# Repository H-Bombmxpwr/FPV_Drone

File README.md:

# FPV Drone Project - ECE 445

This repository contains the design and implementation files for the FPV (First-Person View) Drone project developed by Hunter, Eli, and Griffin for the ECE 445 final project at the University of Illinois in the Spring of 2024.

## Project Overview

The FPV Drone project aims to create a robust and user-friendly drone capable of transmitting real-time video to the user, providing an immersive flying experience. This project was proposed by John M. Hart from the center of Autonomy at the University of Illinois. This repository includes everything that was used in one way or another to make this project. 

## Directories

- Code
   - Low level arduino and c code for flashing the microcontrollers 
- crazyflie_control
   - Software to control the Crazyflie Drone
   - Firmware to flash the Crazyflie Done
   - Extensive debugging tools for setup
- Documents
   - Power Points
   - Design Documents
   - PCB schematics and gerbers
   - Images
   - Personal notes
   - Needed Documentation

## Getting Started
If you are looking to control the drone with your computer you will need:
- Crazyflie 2.0 Drone
- Crazyradio or Crazyflie PA
- Gaming Controller Controller

Then follow the list of steps in [install.md](install.md). 

## The Project

It can be found at this [link](https://courses.engr.illinois.edu/ece445/projects.asp) under "Spring 2024". We were team 64. To save time some material is also linked below:

- [Design Document](Documents/documentation/Design_Document_ECE_445.pdf)
- [Video](https://youtu.be/XnW3fZcY0gs)
- [Final Paper](Documents/documentation/ECE_445_Final_Paper_ECE445.pdf)

## Acknowledgments

- Jon Hart
- Dennis McCann
- Tianxiang Zheng
- Bitlooney

Project Link: [https://github.com/H-Bombmxpwr/FPV_Drone](https://github.com/H-Bombmxpwr/FPV_Drone)

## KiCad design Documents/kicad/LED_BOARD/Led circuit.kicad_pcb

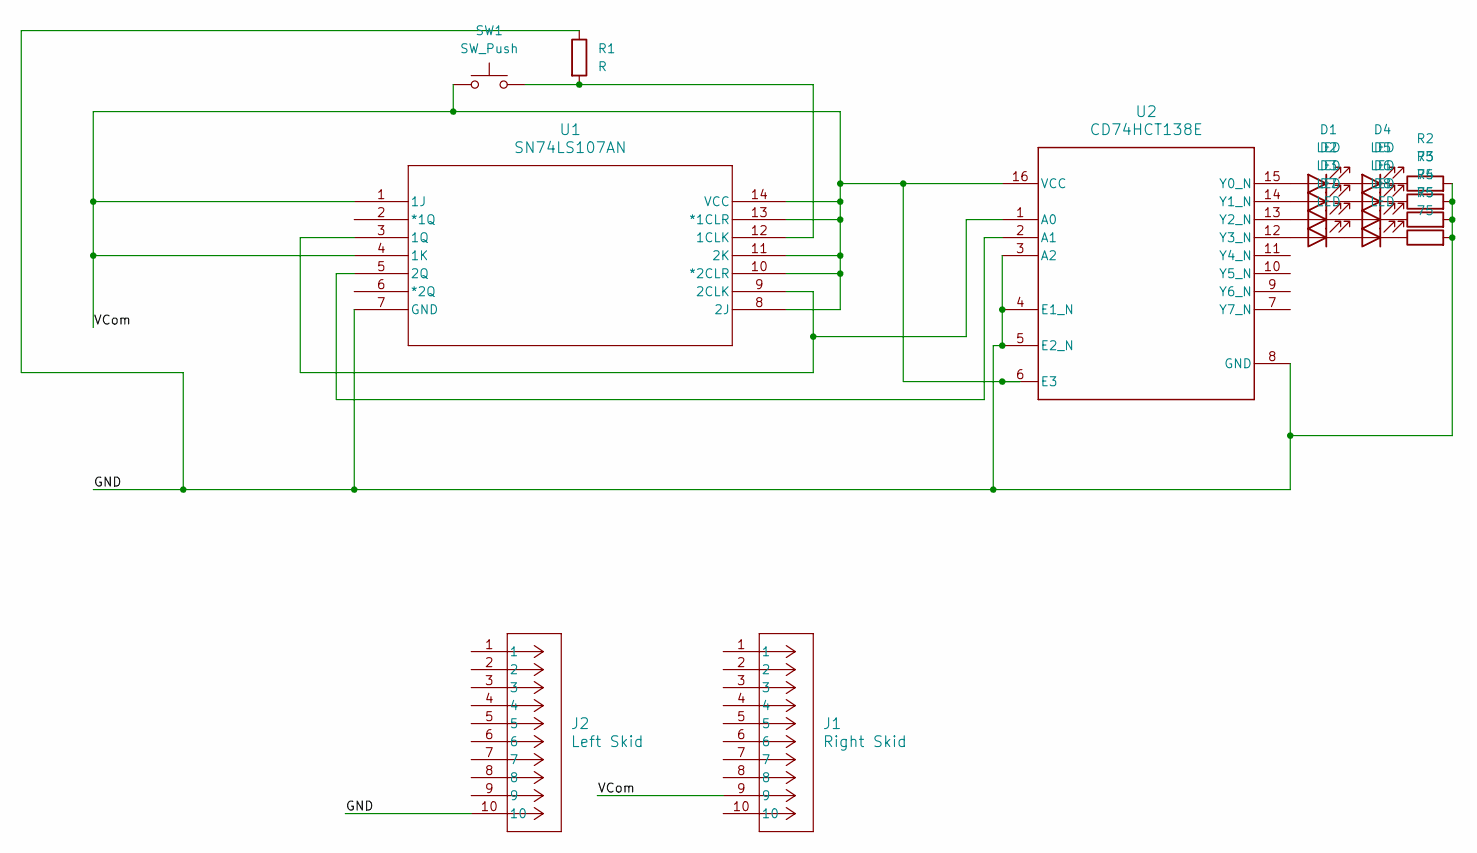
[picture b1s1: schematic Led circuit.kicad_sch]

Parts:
D1, D2, D3, D4, D5, D6, D7, D8: LED; LED_D2.0mm_W4.8mm_H2.5mm_FlatTop
J1: Right Skid; Connector
J2: Left Skid; Connector
R1: R
R2, R3, R4, R5: 75; R_0805_2012Metric_Pad1.20x1.40mm_HandSolder
SW1: SW_Push
U1: SN74LS107AN
U2: CD74HCT138E

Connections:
/GND: J2.10, R1.1, R2.2, R3.2, R4.2, R5.2, U1.7 (GND), U2.3 (A2), U2.4 (E1_N), U2.5 (E2_N), U2.8 (GND); also elsewhere on the board
/VCom: J1.9, SW1.1, U1.1 (1J), U1.4 (1K), U1.8 (2J), U1.10 (*2CLR), U1.11 (2K), U1.13 (*1CLR), U1.14 (VCC), U2.6 (E3), U2.16 (VCC)
unnamed: D1.2 (A), U2.15 (Y0_N)
unnamed: D1.1 (K), D4.2 (A)
unnamed: D2.2 (A), U2.14 (Y1_N)
unnamed: D2.1 (K), D5.2 (A)
unnamed: D3.2 (A), U2.13 (Y2_N)
unnamed: D3.1 (K), D6.2 (A)
unnamed: D4.1 (K), R2.1
unnamed: D5.1 (K), R3.1
unnamed: D6.1 (K), R4.1
unnamed: D7.2 (A), U2.12 (Y3_N)
unnamed: D7.1 (K), D8.2 (A)
unnamed: D8.1 (K), R5.1
unnamed 14: R1.2, SW1.2, U1.12 (1CLK); also elsewhere on the board
unnamed: U1.3 (1Q), U1.9 (2CLK), U2.1 (A0)
unnamed: U1.5 (2Q), U2.2 (A1)

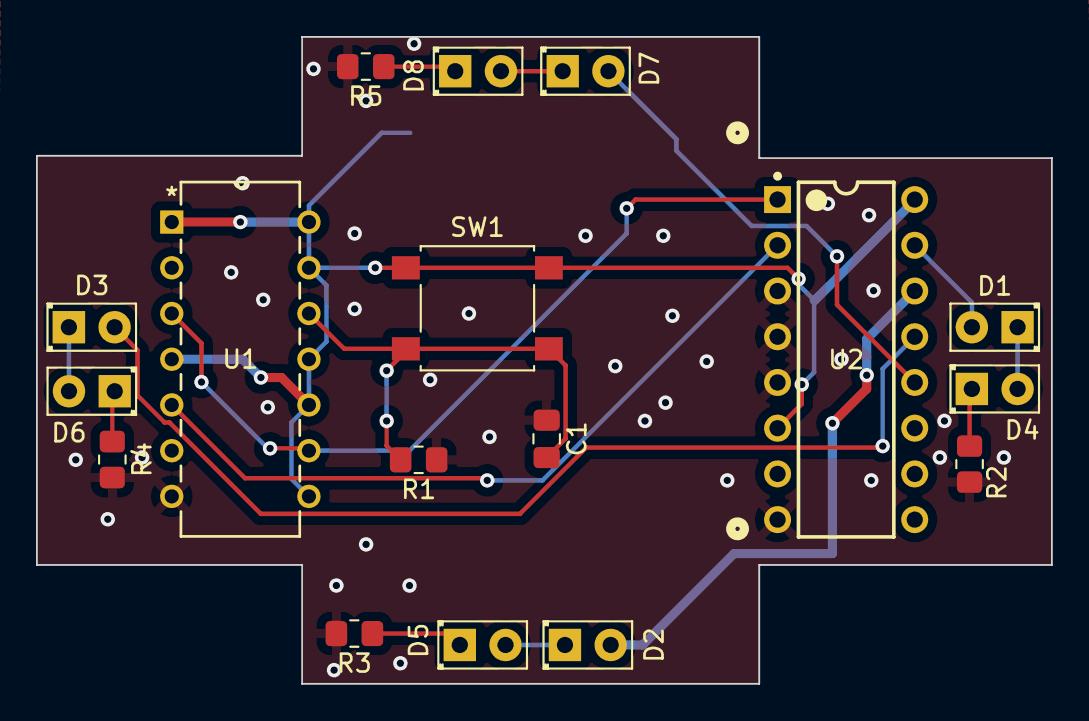
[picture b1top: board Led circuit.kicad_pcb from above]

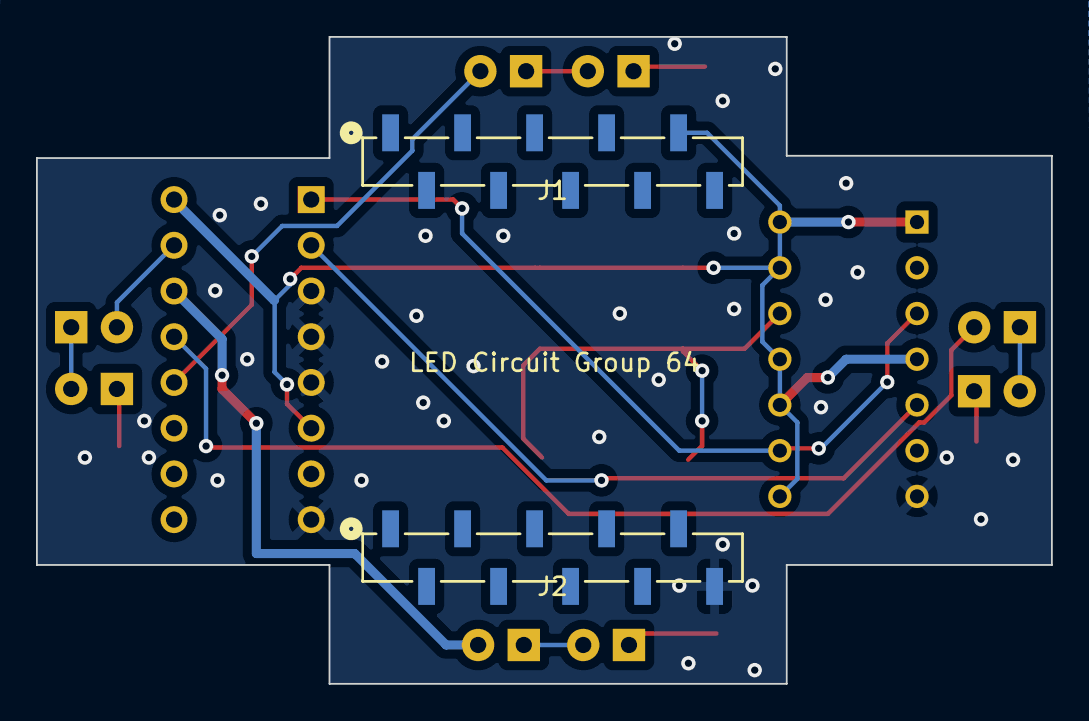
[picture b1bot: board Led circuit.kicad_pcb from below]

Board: 2 copper layers, 56.4 x 35.9 mm, 19 parts (2 on the bottom side), 17 nets.

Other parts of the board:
C1: C; C_0805_2012Metric_Pad1.18x1.45mm_HandSolder

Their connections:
/GND: C1.1; also elsewhere on the board
unnamed 14: C1.2; also elsewhere on the board

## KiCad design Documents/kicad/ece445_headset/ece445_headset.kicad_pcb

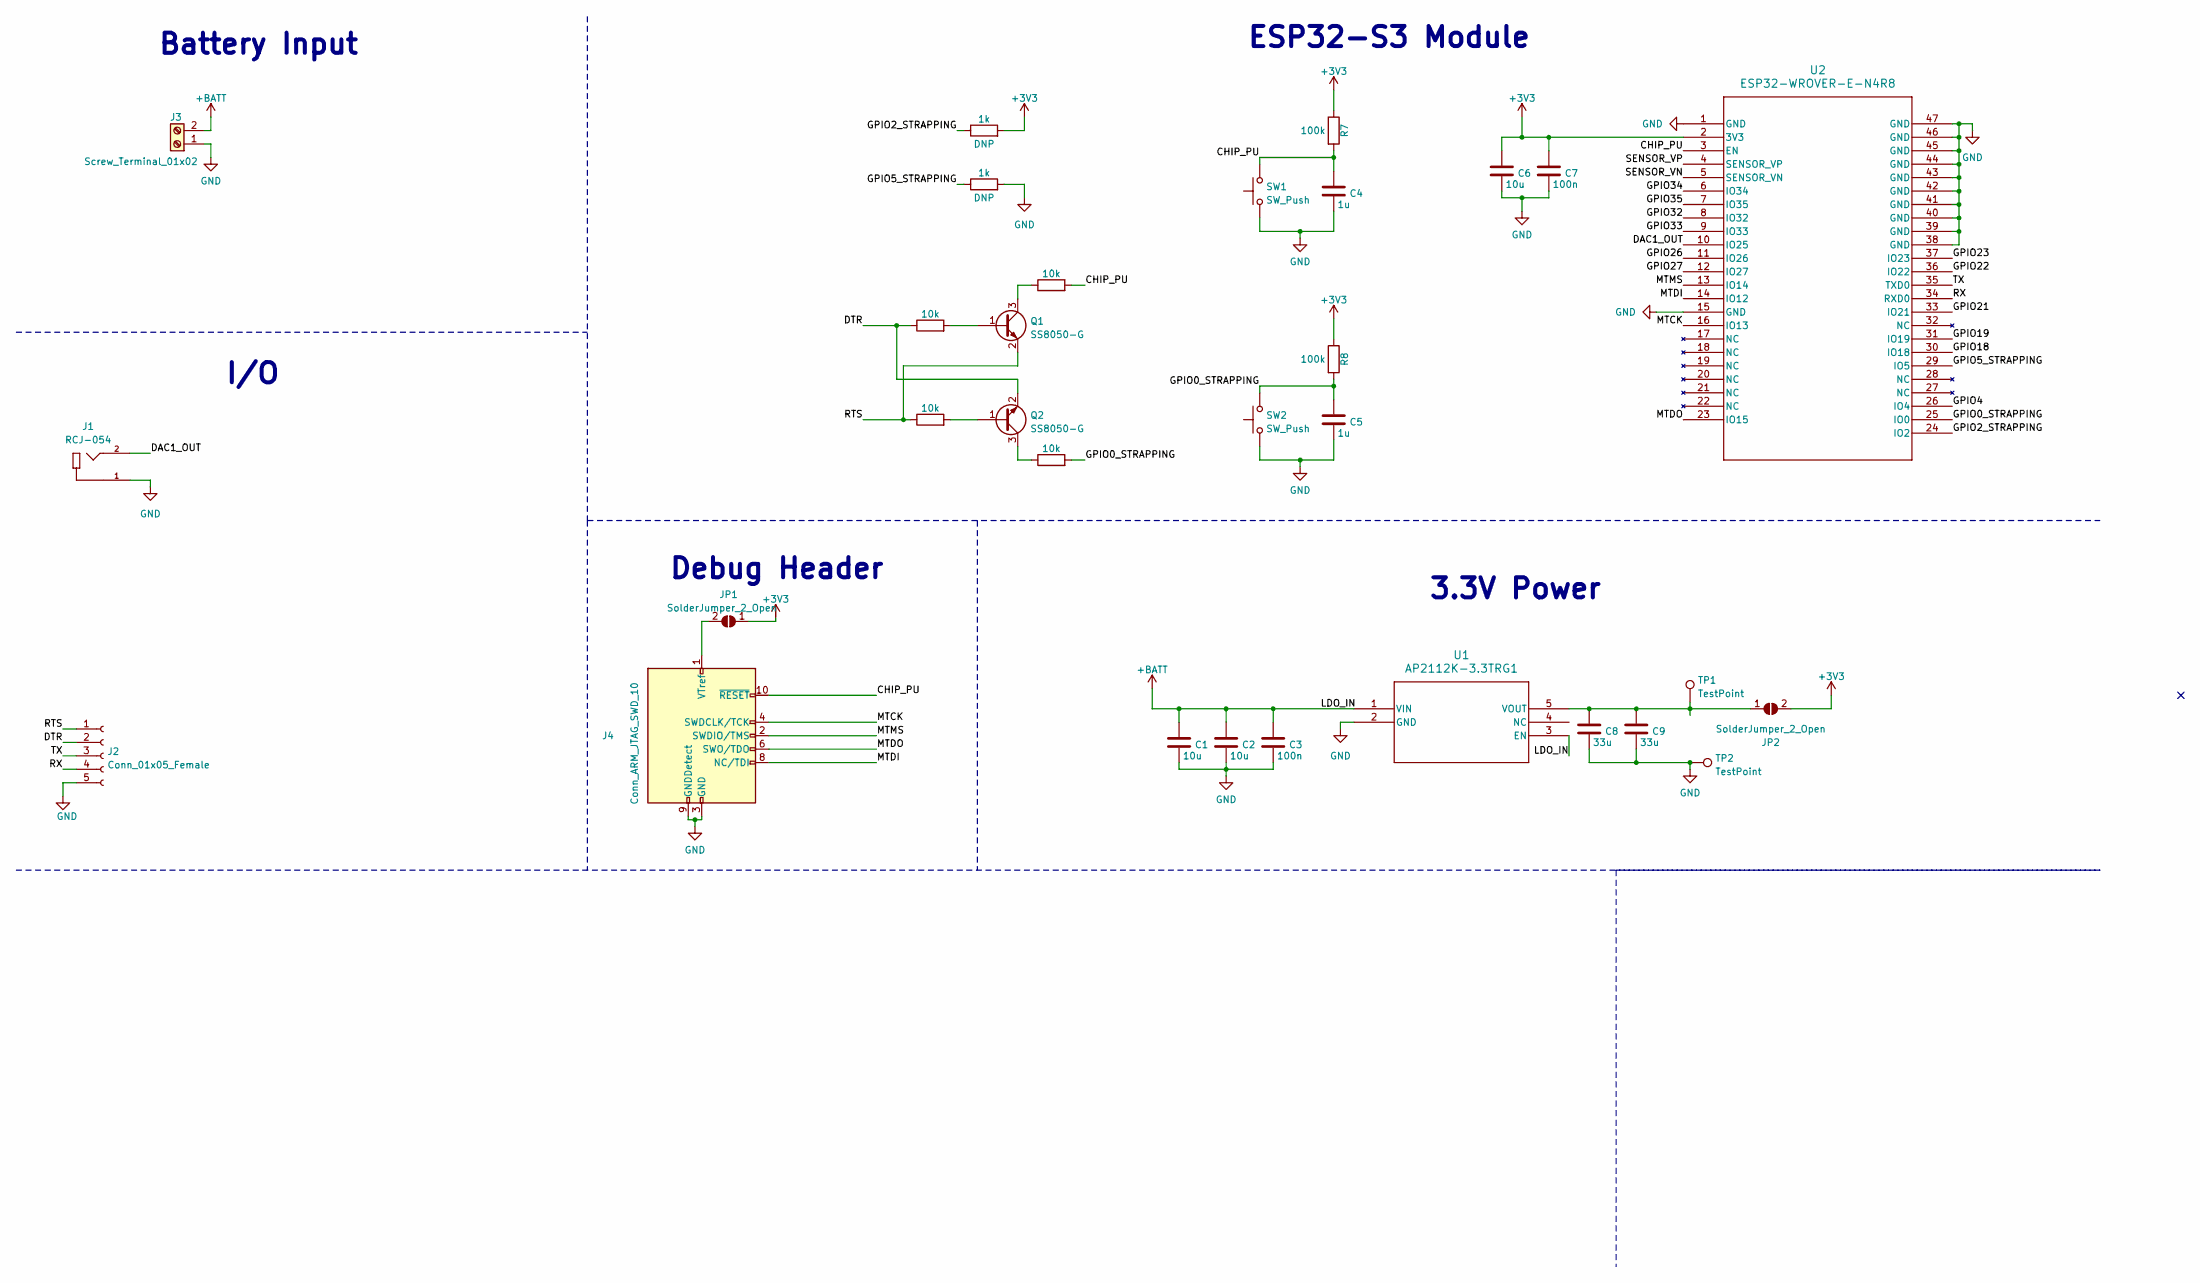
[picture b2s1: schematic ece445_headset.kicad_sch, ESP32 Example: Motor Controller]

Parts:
C1, C2, C6: 10u; C_0805_2012Metric
C3, C7: 100n; C_0805_2012Metric
C4, C5: 1u; C_0805_2012Metric
C8, C9: 33u; C_0805_2012Metric
J1: RCJ-054; CUI_RCJ-054
J2: Conn_01x05_Female; PinHeader_1x05_P2.54mm_Vertical
J3: Screw_Terminal_01x02; TerminalBlock_Phoenix_MKDS-1,5-2-5.08_1x02_P5.08mm_Horizont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
J4: Conn_ARM_JTAG_SWD_10; IDC-Header_2x05_P2.54mm_Vertical
JP1, JP2: SolderJumper_2_Open; SolderJumper-2_P1.3mm_Open_TrianglePad1.0x1.5mm
Q1, Q2: SS8050-G; SOT-23
R1, R2, R5, R6: 10k; R_0805_2012Metric
R3, R4: 1k; R_0805_2012Metric
R7, R8: 100k; R_0805_2012Metric
SW1, SW2: SW_Push; SW_SPST_B3S-1000
TP1, TP2: TestPoint; TestPoint_Keystone_5010-5014_Multipurpose
U1: AP2112K-3.3TRG1; SOT95P285X140-5N
U2: ESP32-WROVER-E-N4R8; ESP32­WROVER­E&slash_ESP32­WROVER­IE_EXP

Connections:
+3V3: C6.1, C7.1, JP1.1 (A), JP2.2 (B), R3.2, R7.1, R8.1, U2.2 (3V3)
+BATT: C1.1, C2.1, C3.1, J3.2, U1.1 (VIN), U1.3 (EN)
/CHIP_PU: C4.1, J4.10 (~RESET), R5.2, R7.2, SW1.2, U2.3 (EN)
/DAC1_OUT: J1.2, U2.10 (IO25)
/DTR: J2.2, Q2.2 (E), R1.1
/GPIO0_STRAPPING: C5.1, R6.2, R8.2, SW2.2, U2.25 (IO0)
/GPIO2_STRAPPING: R3.1, U2.24 (IO2)
/GPIO4: U2.26 (IO4)
/GPIO5_STRAPPING: R4.1, U2.29 (IO5)
/GPIO18: U2.30 (IO18)
/GPIO19: U2.31 (IO19)
/GPIO21: U2.33 (IO21)
/GPIO22: U2.36 (IO22)
/GPIO23: U2.37 (IO23)
/GPIO26: U2.11 (IO26)
/GPIO27: U2.12 (IO27)
/GPIO32: U2.8 (IO32)
/GPIO33: U2.9 (IO33)
/GPIO34: U2.6 (IO34)
/GPIO35: U2.7 (IO35)
/MTCK: J4.4 (SWDCLK/TCK), U2.16 (IO13)
/MTDI: J4.8 (NC/TDI), U2.14 (IO12)
/MTDO: J4.6 (SWO/TDO), U2.23 (IO15)
/MTMS: J4.2 (SWDIO/TMS), U2.13 (IO14)
/RTS: J2.1, Q1.2 (E), R2.1
/RX: J2.4, U2.34 (RXD0)
/SENSOR_VN: U2.5 (SENSOR_VN)
/SENSOR_VP: U2.4 (SENSOR_VP)
/TX: J2.3, U2.35 (TXD0)
GND: C1.2, C2.2, C3.2, C4.2, C5.2, C6.2, C7.2, C8.2, C9.2, J1.1, J2.5, J3.1, J4.3 (GND), J4.5 (GND), J4.9 (GNDDetect), R4.2, SW1.1, SW2.1, TP2.1, U1.2 (GND), U2.1 (GND), U2.15 (GND), U2.38 (GND), U2.39 (GND), U2.40 (GND), U2.41 (GND), U2.42 (GND), U2.43 (GND), U2.44 (GND), U2.45 (GND), U2.46 (GND), U2.47 (GND)
unnamed: J4.1 (VTref), JP1.2 (B)
unnamed: C8.1, C9.1, JP2.1 (A), TP1.1, U1.5 (VOUT)
unnamed: Q1.1 (B), R1.2
unnamed: Q1.3 (C), R5.1
unnamed: Q2.1 (B), R2.2
unnamed: Q2.3 (C), R6.1

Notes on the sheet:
ESP32-S3 Module
Debug Header
3.3V Power
Battery Input
I/O

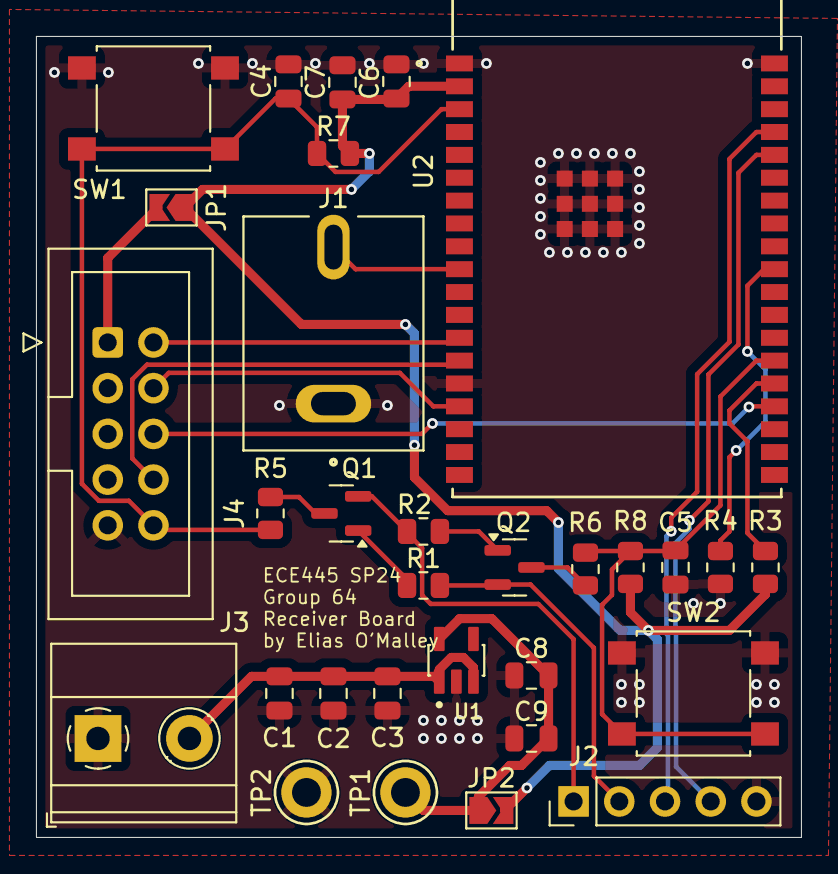
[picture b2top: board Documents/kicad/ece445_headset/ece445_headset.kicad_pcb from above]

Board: 2 copper layers, 42.5 x 44.5 mm, 31 parts (0 on the bottom side), 22 nets.

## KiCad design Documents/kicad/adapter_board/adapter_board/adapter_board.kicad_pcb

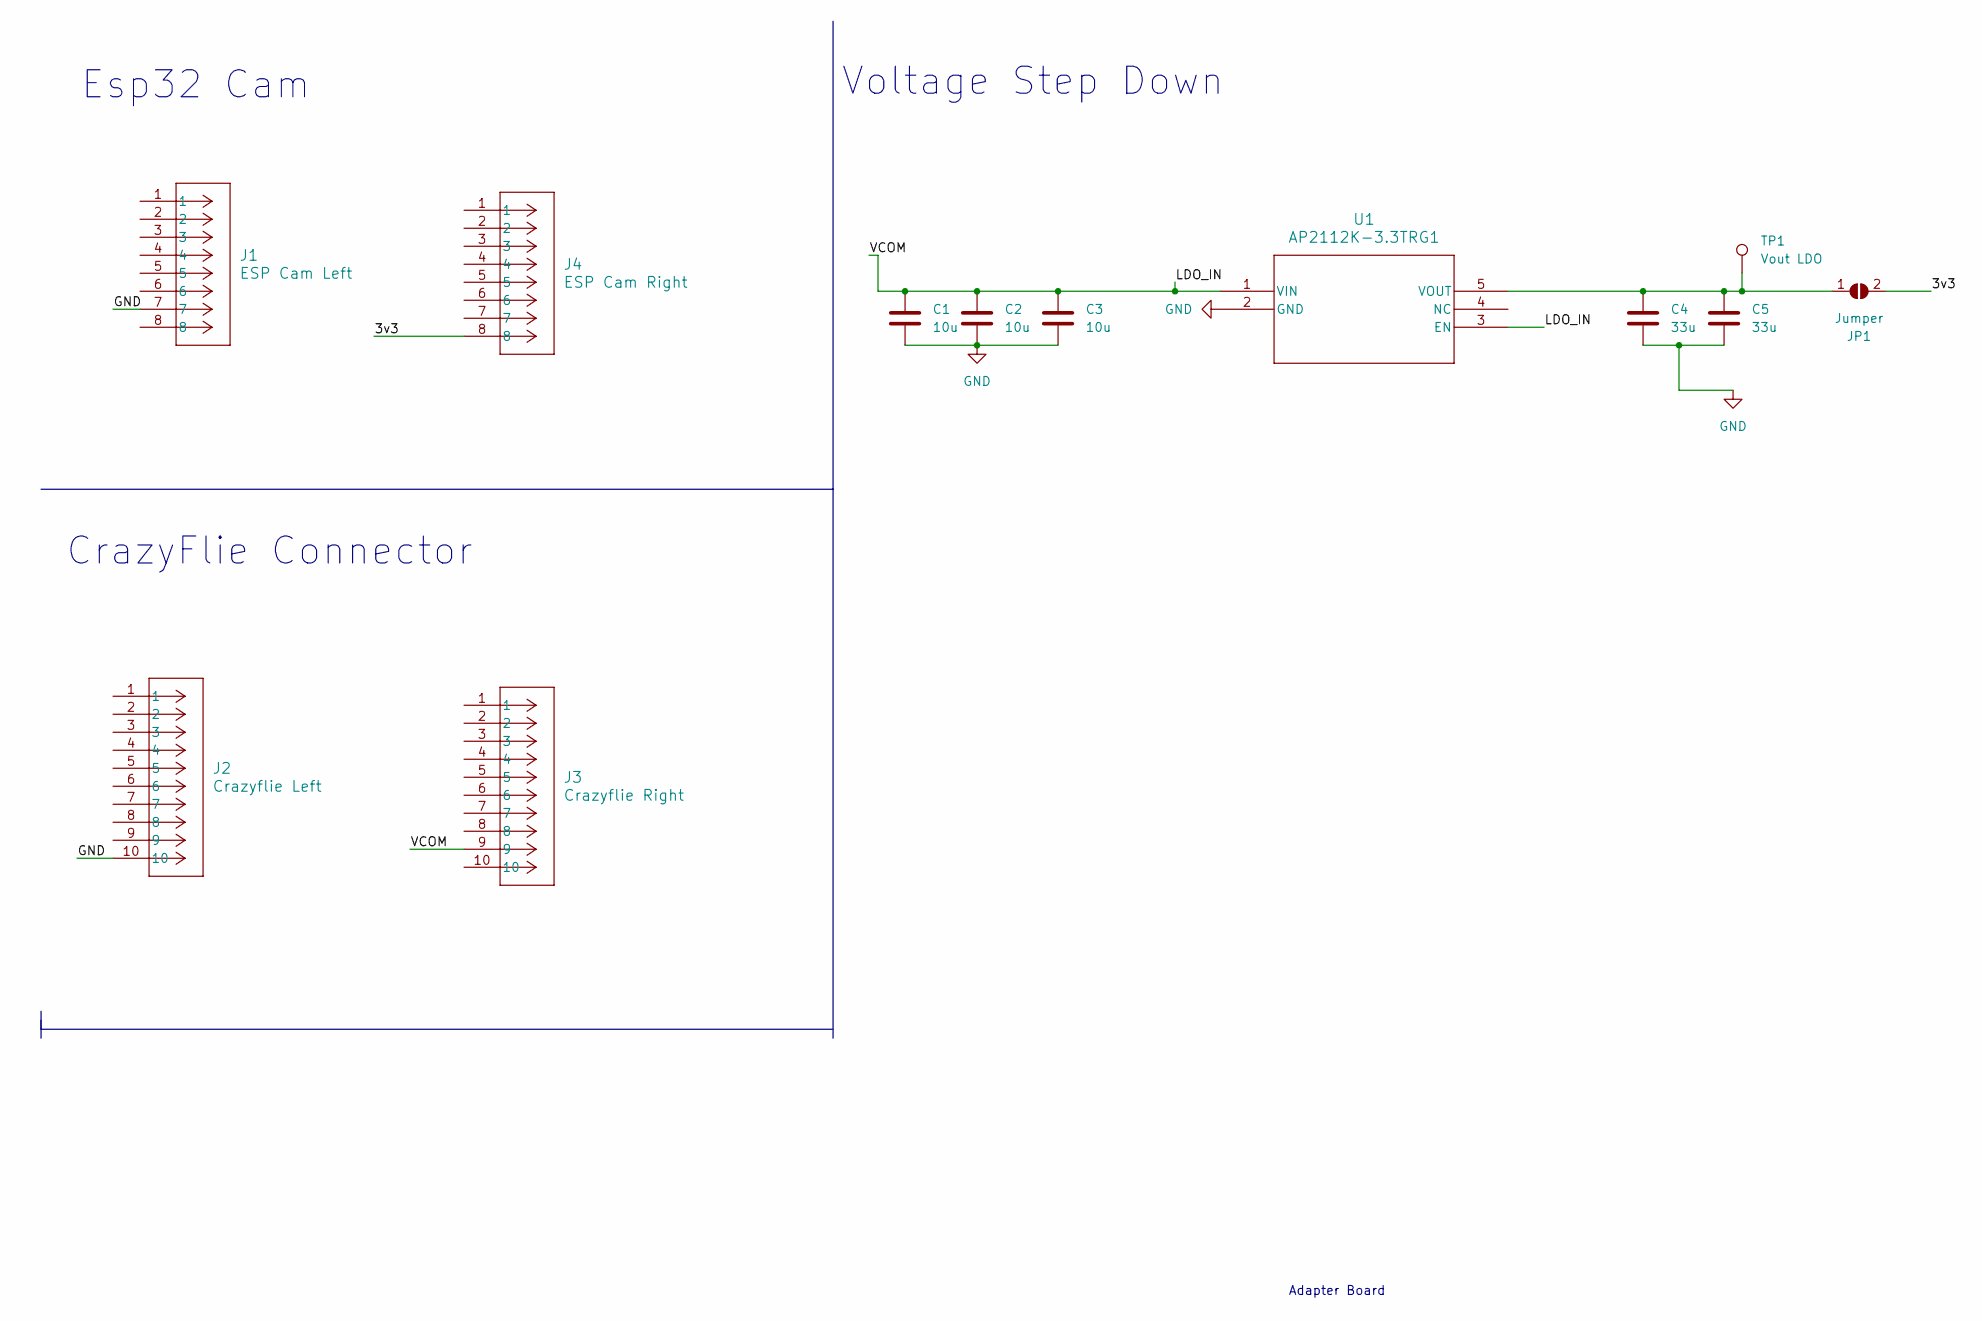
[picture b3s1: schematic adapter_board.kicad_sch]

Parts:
C1, C2, C3: 10u; C_0805_2012Metric_Pad1.18x1.45mm_HandSolder
C4, C5: 33u; C_0805_2012Metric_Pad1.18x1.45mm_HandSolder
J1: ESP Cam Left; CONN_NPTC081KFXC-RC_SUL
J2: Crazyflie Left; CONN10X1_NPPN101BFLC-RC_SUL
J3: Crazyflie Right; CONN10X1_NPPN101BFLC-RC_SUL
J4: ESP Cam Right; CONN_NPTC081KFXC-RC_SUL
JP1: Jumper; SolderJumper-2_P1.3mm_Open_TrianglePad1.0x1.5mm
TP1: Vout LDO; TestPoint_THTPad_1.5x1.5mm_Drill0.7mm
U1: AP2112K-3.3TRG1; SOT95P285X140-5N

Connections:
/3v3: J4.8, JP1.2 (B)
/LDO_IN: C1.1, C2.1, C3.1, J3.9, U1.1 (VIN), U1.3 (EN)
GND: C1.2, C2.2, C3.2, C4.2, C5.2, J1.7, J2.10, U1.2 (GND)
unnamed: C4.1, C5.1, JP1.1 (A), TP1.1, U1.5 (VOUT)

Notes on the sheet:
Adapter Board
Voltage Step Down
Esp32 Cam
CrazyFlie Connector

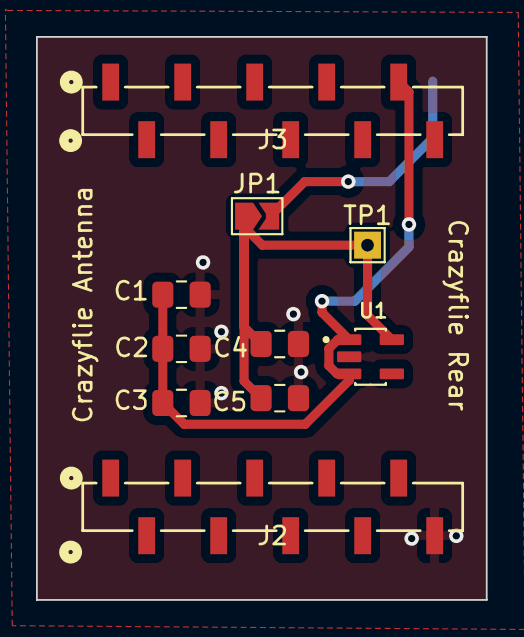
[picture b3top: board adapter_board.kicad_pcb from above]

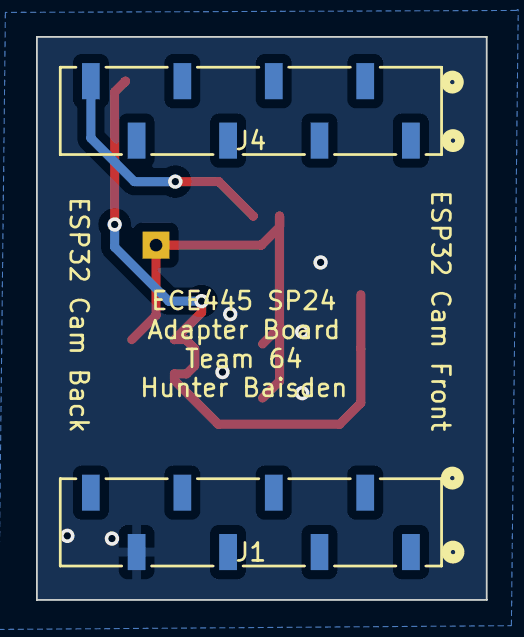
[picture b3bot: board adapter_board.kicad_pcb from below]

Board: 2 copper layers, 25.0 x 31.3 mm, 12 parts (2 on the bottom side), 4 nets.

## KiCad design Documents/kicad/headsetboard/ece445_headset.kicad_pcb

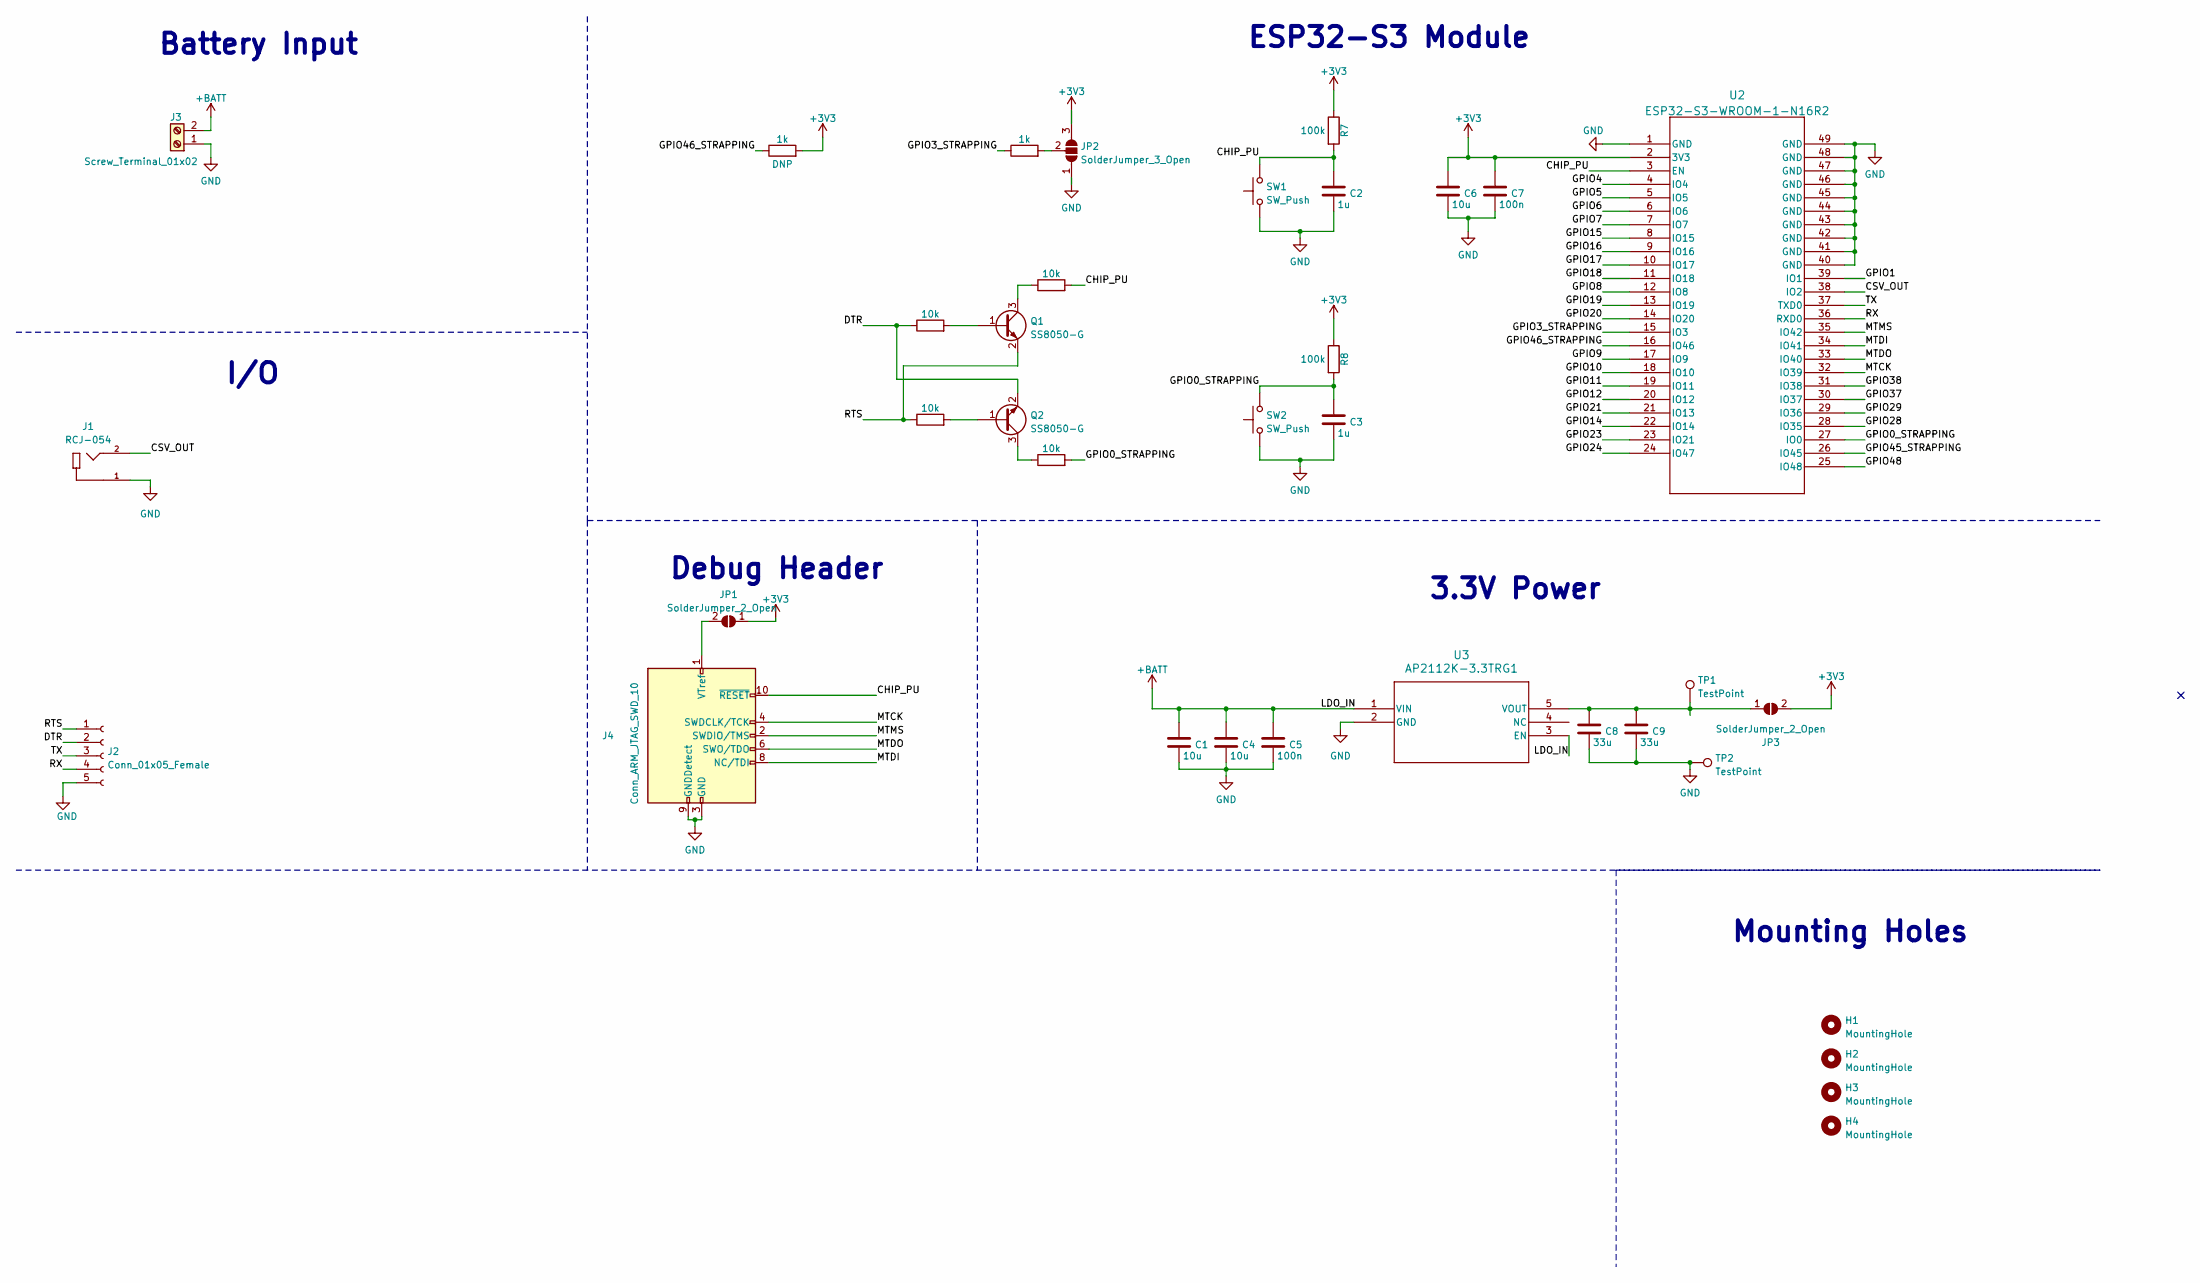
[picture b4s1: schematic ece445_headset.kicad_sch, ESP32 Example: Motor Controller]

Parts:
C1, C4, C6: 10u; C_0805_2012Metric
C2, C3: 1u; C_0805_2012Metric
C5, C7: 100n; C_0805_2012Metric
C8, C9: 33u; C_0805_2012Metric
H1, H2, H3, H4: MountingHole; MountingHole_3.2mm_M3
J1: RCJ-054; CUI_RCJ-054
J2: Conn_01x05_Female; PinHeader_1x05_P2.54mm_Vertical
J3: Screw_Terminal_01x02; TerminalBlock_Phoenix_MKDS-1,5-2-5.08_1x02_P5.08mm_Horizont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
J4: Conn_ARM_JTAG_SWD_10; IDC-Header_2x05_P2.54mm_Vertical
JP1, JP3: SolderJumper_2_Open; SolderJumper-2_P1.3mm_Open_TrianglePad1.0x1.5mm
JP2: SolderJumper_3_Open; SolderJumper-3_P2.0mm_Open_TrianglePad1.0x1.5mm
Q1, Q2: SS8050-G; SOT-23
R1, R4: 1k; R_0805_2012Metric
R2, R3, R5, R6: 10k; R_0805_2012Metric
R7, R8: 100k; R_0805_2012Metric
SW1, SW2: SW_Push; SW_SPST_B3S-1000
TP1, TP2: TestPoint; TestPoint_Keystone_5010-5014_Multipurpose
U2: ESP32-S3-WROOM-1-N16R2; ESP32-S3-WROOM-1_EXP
U3: AP2112K-3.3TRG1; SOT95P285X140-5N

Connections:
+3V3: C6.1, C7.1, JP1.1 (A), JP2.3 (B), JP3.2 (B), R1.2, R7.1, R8.1, U2.2 (3V3)
+BATT: C1.1, C4.1, C5.1, J3.2, U3.1 (VIN), U3.3 (EN)
/CHIP_PU: C2.1, J4.10 (~RESET), R5.2, R7.2, SW1.2, U2.3 (EN)
/CSV_OUT: J1.2, U2.38 (IO2)
/DTR: J2.2, Q2.2 (E), R2.1
/GPIO0_STRAPPING: C3.1, R6.2, R8.2, SW2.2, U2.27 (IO0)
/GPIO1: U2.39 (IO1)
/GPIO3_STRAPPING: R4.1, U2.15 (IO3)
/GPIO4: U2.4 (IO4)
/GPIO5: U2.5 (IO5)
/GPIO6: U2.6 (IO6)
/GPIO7: U2.7 (IO7)
/GPIO8: U2.12 (IO8)
/GPIO9: U2.17 (IO9)
/GPIO10: U2.18 (IO10)
/GPIO11: U2.19 (IO11)
/GPIO12: U2.20 (IO12)
/GPIO14: U2.22 (IO14)
/GPIO15: U2.8 (IO15)
/GPIO16: U2.9 (IO16)
/GPIO17: U2.10 (IO17)
/GPIO18: U2.11 (IO18)
/GPIO19: U2.13 (IO19)
/GPIO20: U2.14 (IO20)
/GPIO21: U2.21 (IO13)
/GPIO23: U2.23 (IO21)
/GPIO24: U2.24 (IO47)
/GPIO28: U2.28 (IO35)
/GPIO29: U2.29 (IO36)
/GPIO37: U2.30 (IO37)
/GPIO38: U2.31 (IO38)
/GPIO45_STRAPPING: U2.26 (IO45)
/GPIO46_STRAPPING: R1.1, U2.16 (IO46)
/GPIO48: U2.25 (IO48)
/MTCK: J4.4 (SWDCLK/TCK), U2.32 (IO39)
/MTDI: J4.8 (NC/TDI), U2.34 (IO41)
/MTDO: J4.6 (SWO/TDO), U2.33 (IO40)
/MTMS: J4.2 (SWDIO/TMS), U2.35 (IO42)
/RTS: J2.1, Q1.2 (E), R3.1
/RX: J2.4, U2.36 (RXD0)
/TX: J2.3, U2.37 (TXD0)
GND: C1.2, C2.2, C3.2, C4.2, C5.2, C6.2, C7.2, C8.2, C9.2, J1.1, J2.5, J3.1, J4.3 (GND), J4.5 (GND), J4.9 (GNDDetect), JP2.1 (A), SW1.1, SW2.1, TP2.1, U2.1 (GND), U2.40 (GND), U2.41 (GND), U2.42 (GND), U2.43 (GND), U2.44 (GND), U2.45 (GND), U2.46 (GND), U2.47 (GND), U2.48 (GND), U2.49 (GND), U3.2 (GND)
unnamed: J4.1 (VTref), JP1.2 (B)
unnamed: JP2.2 (C), R4.2
unnamed: C8.1, C9.1, JP3.1 (A), TP1.1, U3.5 (VOUT)
unnamed: Q1.1 (B), R2.2
unnamed: Q1.3 (C), R5.1
unnamed: Q2.1 (B), R3.2
unnamed: Q2.3 (C), R6.1

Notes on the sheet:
ESP32-S3 Module
Debug Header
Mounting Holes
3.3V Power
Battery Input
I/O

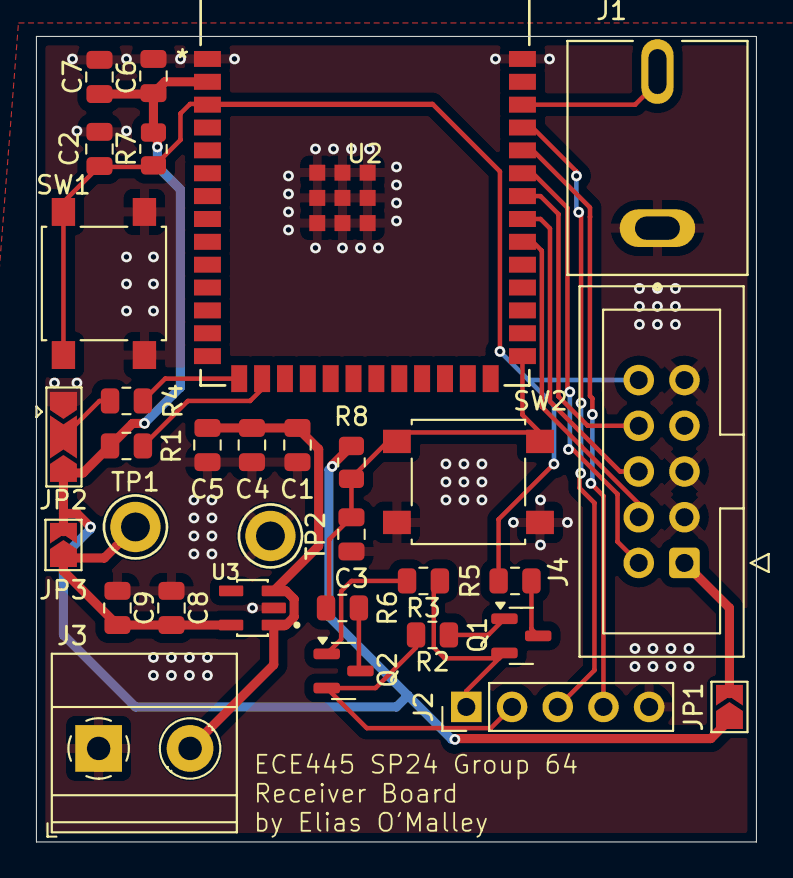
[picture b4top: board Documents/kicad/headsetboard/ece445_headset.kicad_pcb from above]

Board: 2 copper layers, 40.0 x 44.8 mm, 36 parts (0 on the bottom side), 23 nets.
